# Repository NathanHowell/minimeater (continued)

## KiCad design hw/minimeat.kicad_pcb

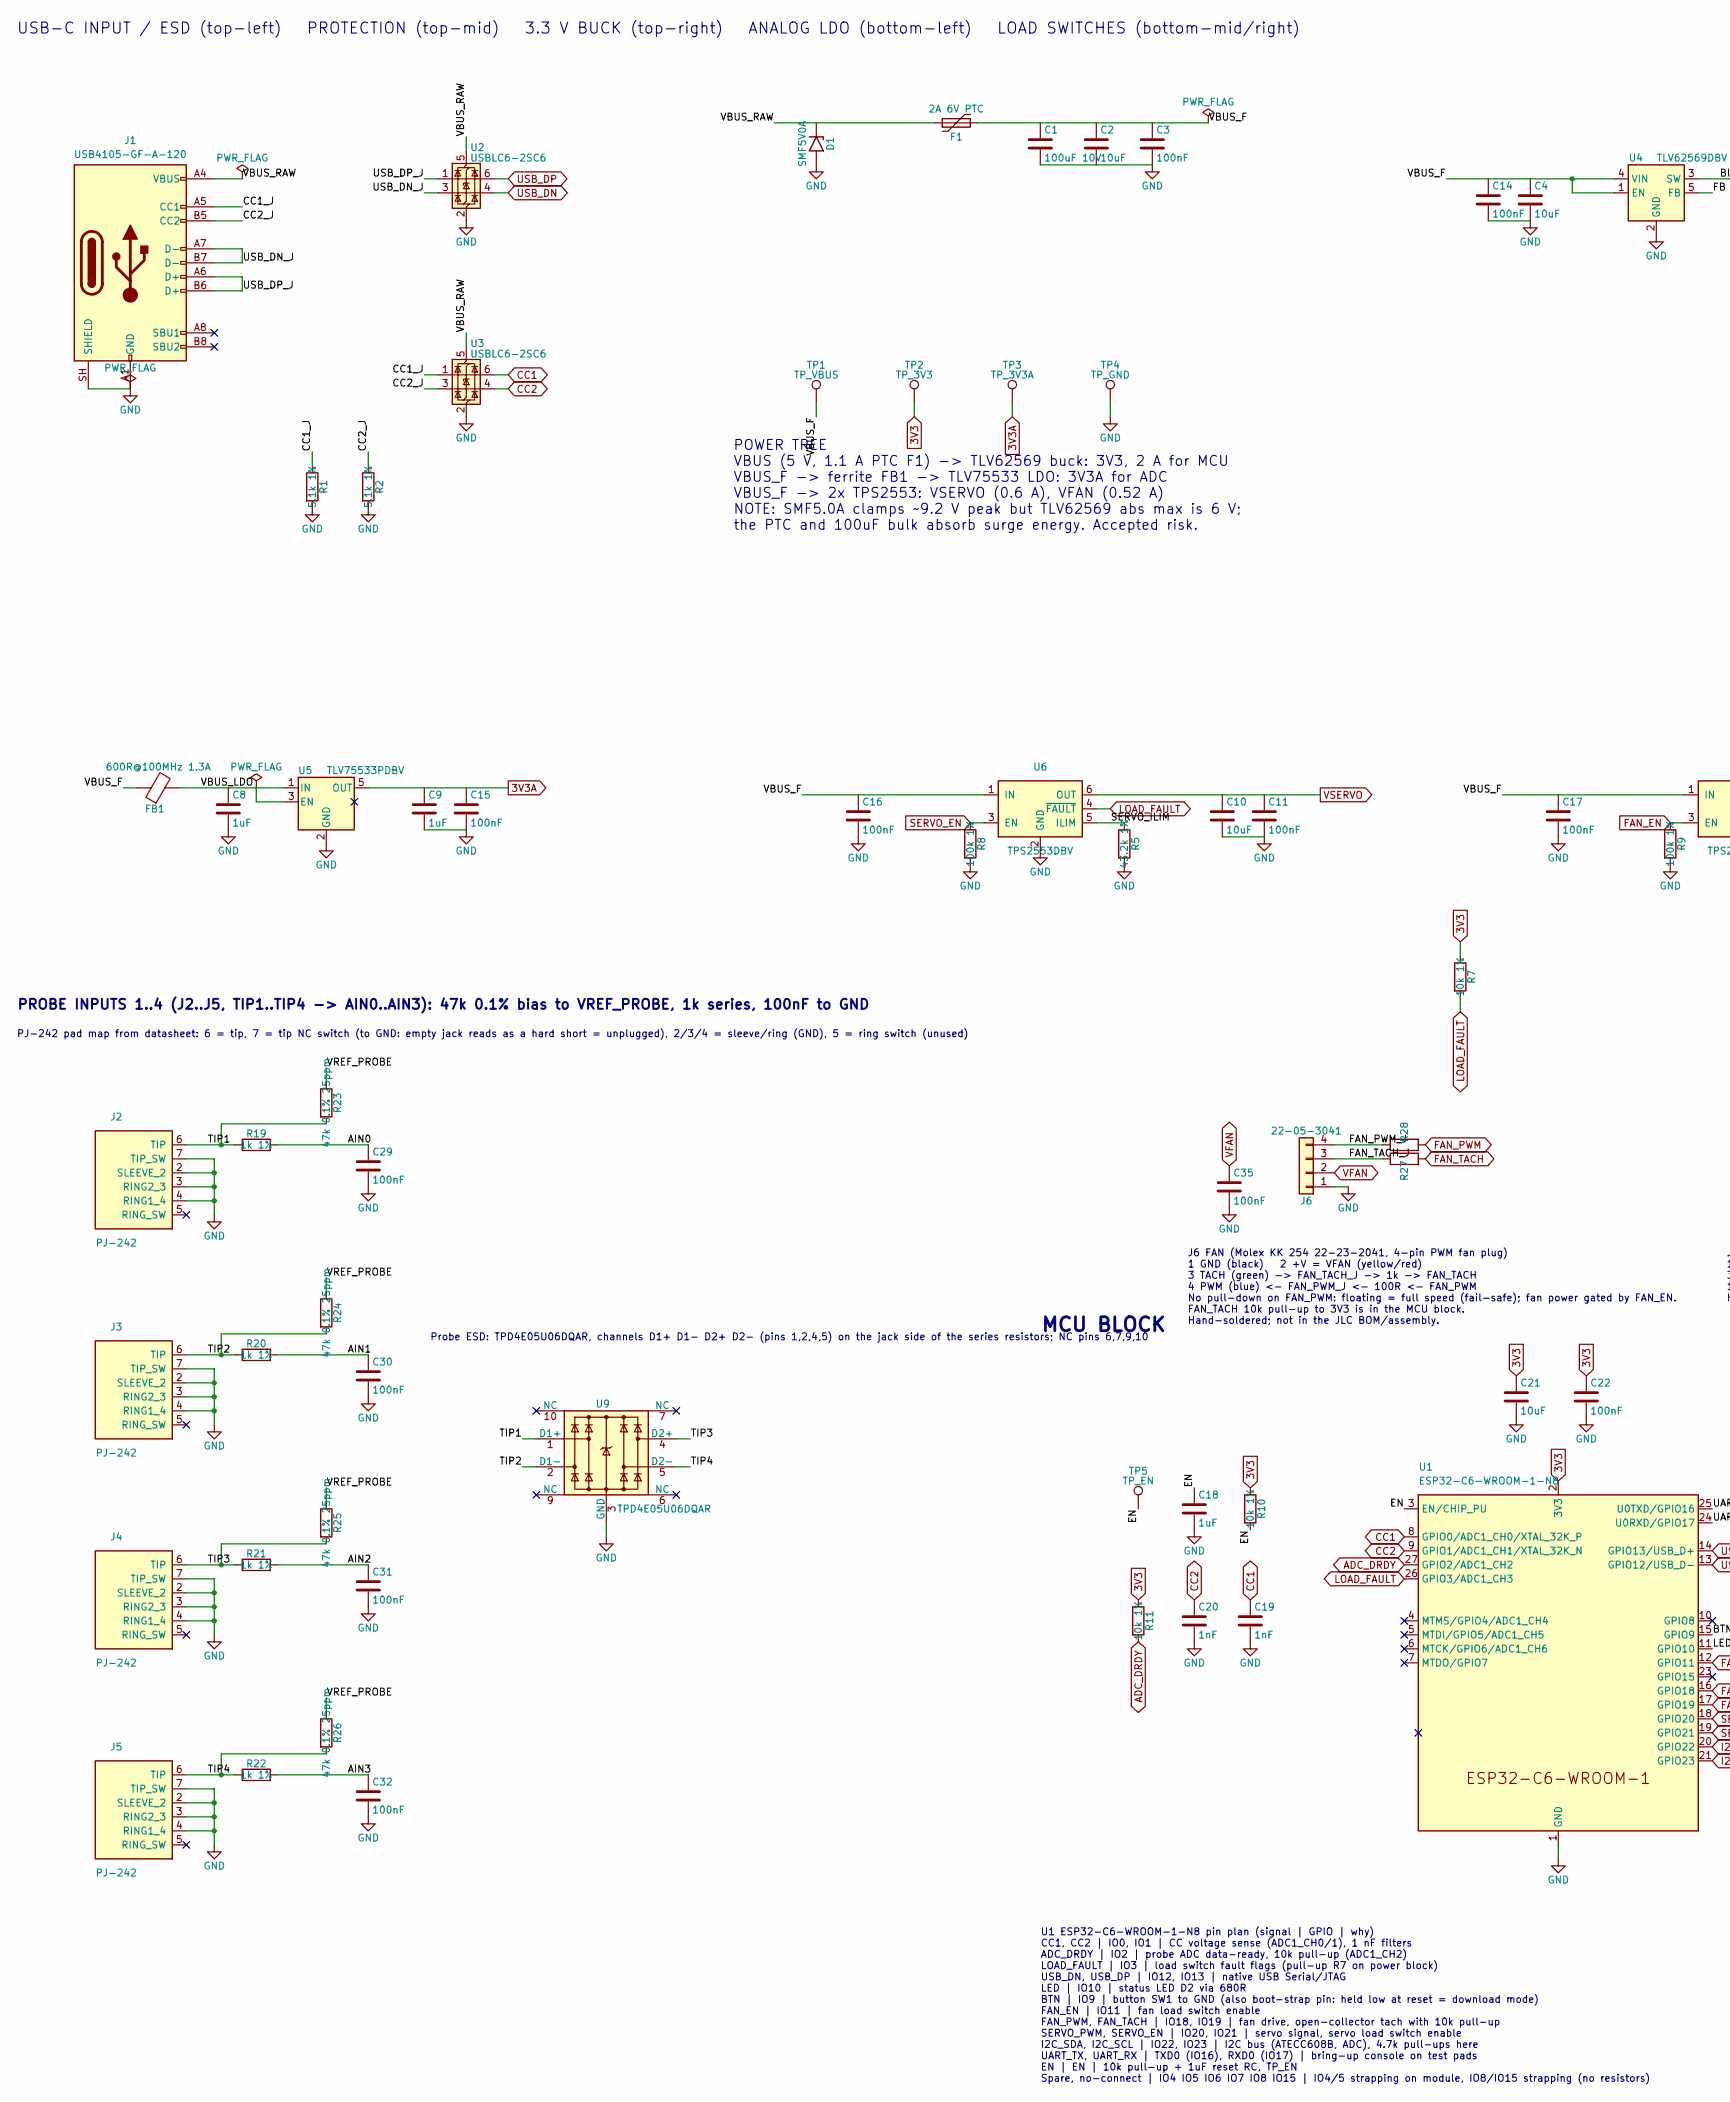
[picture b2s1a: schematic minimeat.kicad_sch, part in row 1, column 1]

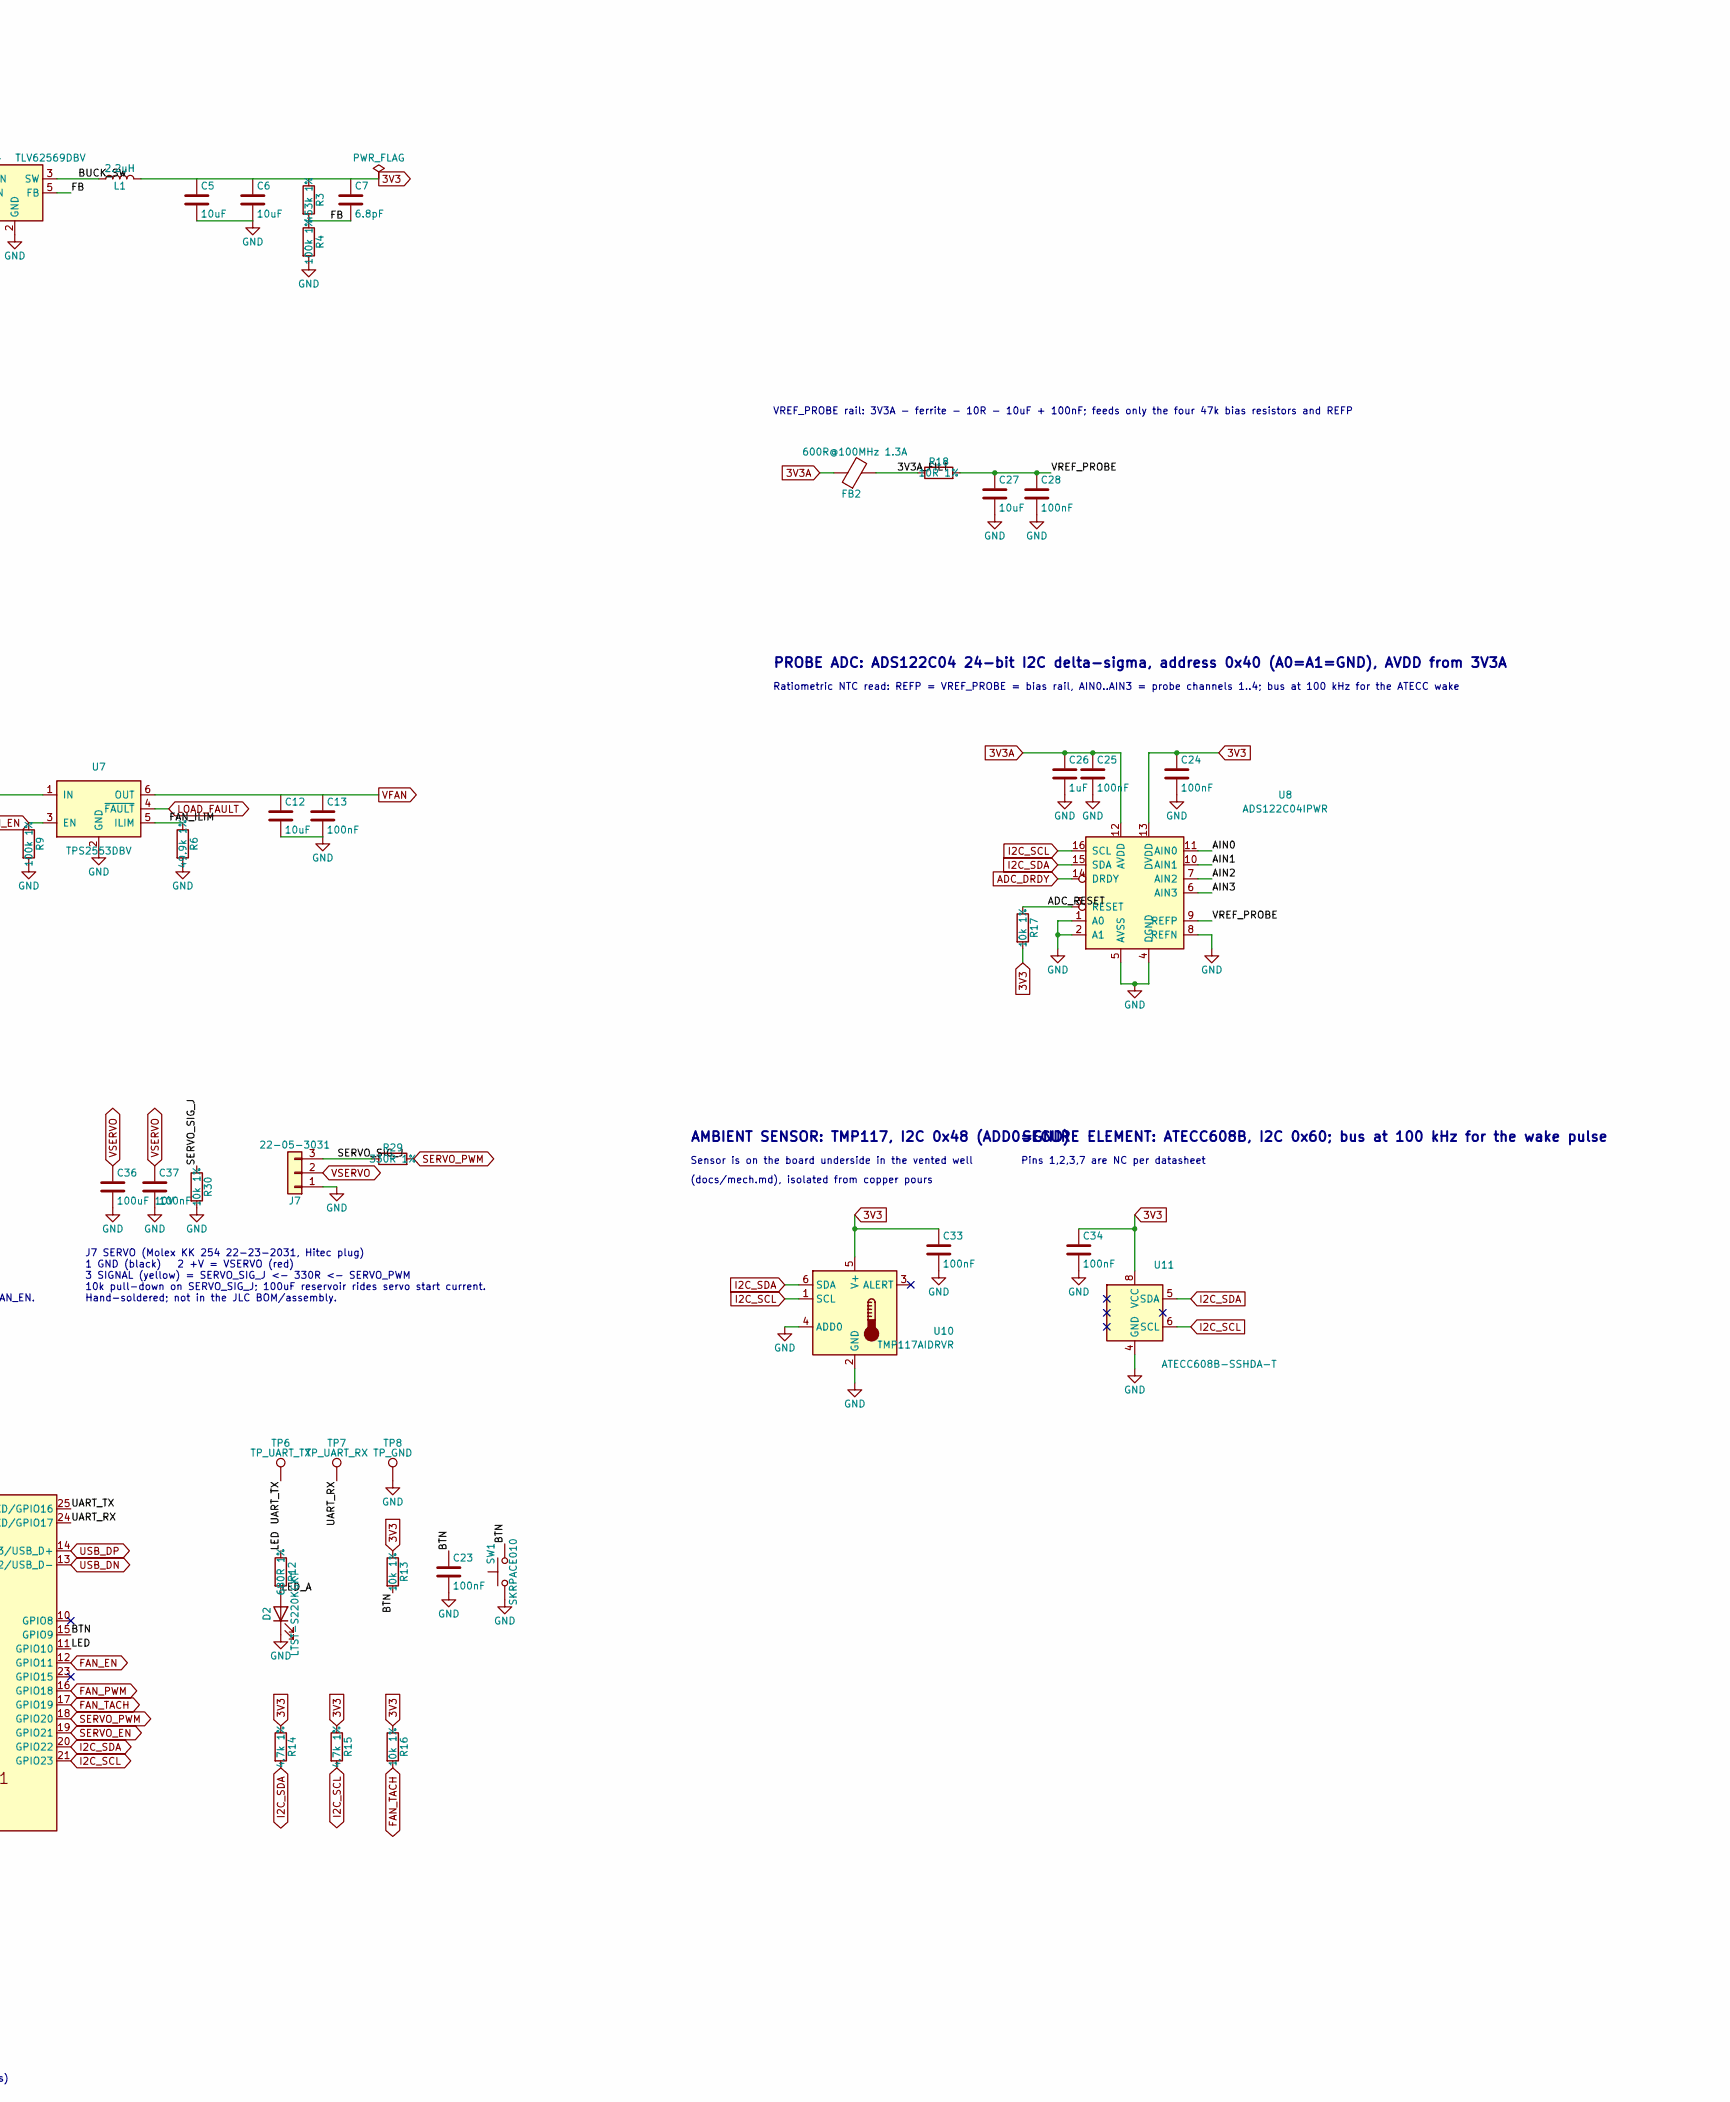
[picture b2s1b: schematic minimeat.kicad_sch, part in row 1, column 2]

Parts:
C1, C36: 100uF 10V; C_1210_3225Metric; LCSC C23742
C2, C4, C5, C6, C10, C12, C21, C27: 10uF; C_0805_2012Metric; LCSC C15850
C3, C11, C13, C14, C15, C16, C17, C22, C23, C24, C25, C28, C29, C30, C31, C32, C33, C34, C35, C37: 100nF; C_0402_1005Metric; LCSC C1525
C7: 6.8pF; C_0402_1005Metric; LCSC C318598
C8, C9, C18, C26: 1uF; C_0402_1005Metric; LCSC C52923
C19, C20: 1nF; C_0402_1005Metric; LCSC C1523
D1: SMF5V0A; D_SMF; LCSC C151296
D2: LTST-S220KGKT; MPN LTST-S220KGKT; LCSC C160469
F1: 2A 6V PTC; Fuse_1206_3216Metric; LCSC C89656
FB1: 600R@100MHz 1.3A; L_0603_1608Metric; LCSC C85833
FB2: 600R@100MHz 1.3A; L_0603_1608Metric; MPN BLM18KG601SN1D; LCSC C85833
J1: USB4105-GF-A-120; USB_C_Receptacle_GCT_USB4105-xx-A_16P_TopMnt_Horizontal; LCSC C5184243
J2, J3, J4, J5: PJ-242; MPN PJ-242; LCSC C431536
J6: 22-05-3041; KK254-RA-04; LCSC N/A hand-solder (Mouser/Digi-Key 22-05-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
J7: 22-05-3031; KK254-RA-03; LCSC N/A hand-solder (Mouser/Digi-Key 22-05-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
L1: 2.2uH; LQH3NPN2R2MMEL; MPN LQH3NPN2R2MMEL; LCSC C668451
R1, R2: 5.1k 1%; R_0402_1005Metric; LCSC C105872
R3: 453k 1%; R_0402_1005Metric; LCSC C27009
R4, R8, R9: 100k 1%; R_0402_1005Metric; LCSC C60491
R5: 43.2k 1%; R_0402_1005Metric; LCSC C137980
R6: 49.9k 1%; R_0402_1005Metric; LCSC C137969
R7, R10, R11, R13, R16, R17, R30: 10k 1%; R_0402_1005Metric; LCSC C60490
R12: 680R 1%; R_0402_1005Metric; MPN RC0402FR-07680RL; LCSC C137948
R14, R15: 4.7k 1%; R_0402_1005Metric; LCSC C25900
R18: 10R 1%; R_0402_1005Metric; LCSC C25077
R19, R20, R21, R22, R27: 1k 1%; R_0402_1005Metric; LCSC C11702
R23, R24, R25, R26: 47k 0.1% 25ppm; R_0603_1608Metric; MPN TNPW060347K0BEEA; LCSC C2089026
R28: 100R 1%; R_0402_1005Metric; LCSC C25076
R29: 330R 1%; R_0402_1005Metric; LCSC C25104
SW1: SKRPACE010; MPN SKRPACE010; LCSC C139797
TP1: TP_VBUS; TestPoint_Pad_D1.5mm; LCSC N/A (not assembled)
TP2: TP_3V3; TestPoint_Pad_D1.5mm; LCSC N/A (not assembled)
TP3: TP_3V3A; TestPoint_Pad_D1.5mm; LCSC N/A (not assembled)
TP4, TP8: TP_GND; TestPoint_Pad_D1.5mm; LCSC N/A (not assembled)
TP5: TP_EN; TestPoint_Pad_D1.5mm; LCSC N/A (not assembled)
TP6: TP_UART_TX; TestPoint_Pad_D1.5mm; LCSC N/A (not assembled)
TP7: TP_UART_RX; TestPoint_Pad_D1.5mm; LCSC N/A (not assembled)
U1: ESP32-C6-WROOM-1-N8; ESP32-C6-WROOM-1; MPN ESP32-C6-WROOM-1-N8; LCSC C5366877
U2, U3: USBLC6-2SC6; SOT-23-6; LCSC C7519
U4: TLV62569DBV; SOT-23-5; LCSC C141836
U5: TLV75533PDBV; SOT-23-5; LCSC C404027
U6, U7: TPS2553DBV; SOT-23-6; LCSC C55266
U8: ADS122C04IPWR; TSSOP-16_4.4x5mm_P0.65mm; MPN ADS122C04IPWR; LCSC C2872338
U9: TPD4E05U06DQAR; TPD4E05U06DQA; MPN TPD4E05U06DQAR; LCSC C138714
U10: TMP117AIDRVR; TMP117AIDRV_WSON-6_noEP; MPN TMP117AIDRVR; LCSC C699536
U11: ATECC608B-SSHDA-T; SOIC-8_3.9x4.9mm_P1.27mm; MPN ATECC608B-SSHDA-T; LCSC C1518769

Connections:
3V3A: C9.1, C15.1, C25.1, C26.1, FB2.1, TP3.1 (1_1), U5.5 (OUT), U8.12 (AVDD)
/3V3A_FILT: FB2.2, R18.1
/ADC_RESET: R17.1, U8.3 (RESET)
/AIN0: C29.1, R19.2, U8.11 (AIN0)
/AIN1: C30.1, R20.2, U8.10 (AIN1)
/AIN2: C31.1, R21.2, U8.7 (AIN2)
/AIN3: C32.1, R22.2, U8.6 (AIN3)
/BTN: C23.1, R13.2, SW1.2, U1.15 (GPIO9)
/BUCK_SW: L1.1, U4.3 (SW)
/CC1_J: J1.A5 (CC1), R1.1, U3.1 (I/O1)
/CC2_J: J1.B5 (CC2), R2.1, U3.3 (I/O2)
/EN: C18.1, R10.2, TP5.1 (1_1), U1.3 (EN/CHIP_PU)
/FAN_ILIM: R6.1, U7.5 (ILIM)
/FAN_PWM_J: J6.4, R28.1
/FAN_TACH_J: J6.3, R27.1
/FB: C7.2, R3.2, R4.1, U4.5 (FB)
/LED: R12.1, U1.11 (GPIO10)
/LED_A: D2.2 (A), R12.2
/SERVO_ILIM: R5.1, U6.5 (ILIM)
/SERVO_SIG_J: J7.3, R29.1, R30.1
/TIP1: J2.6 (TIP), R19.1, R23.2, U9.1 (D1+)
/TIP2: J3.6 (TIP), R20.1, R24.2, U9.2 (D1-)
/TIP3: J4.6 (TIP), R21.1, R25.2, U9.4 (D2+)
/TIP4: J5.6 (TIP), R22.1, R26.2, U9.5 (D2-)
/UART_RX: TP7.1 (1_1), U1.24 (U0RXD/GPIO17)
/UART_TX: TP6.1 (1_1), U1.25 (U0TXD/GPIO16)
/USB_DN_J: J1.A7 (D-), J1.B7 (D-), U2.3 (I/O2)
/USB_DP_J: J1.A6 (D+), J1.B6 (D+), U2.1 (I/O1)
/VREF_PROBE: C27.1, C28.1, R18.2, R23.1, R24.1, R25.1, R26.1, U8.9 (REFP)
ADC_DRDY: R11.2, U1.27 (GPIO2/ADC1_CH2), U8.14 (DRDY)
CC1: C19.1, U1.8 (GPIO0/ADC1_CH0/XTAL_32K_P), U3.6 (I/O1)
CC2: C20.1, U1.9 (GPIO1/ADC1_CH1/XTAL_32K_N), U3.4 (I/O2)
FAN_EN: R9.1, U1.12 (GPIO11), U7.3 (EN)
FAN_PWM: R28.2, U1.16 (GPIO18)
FAN_TACH: R16.2, R27.2, U1.17 (GPIO19)
I2C_SCL: R15.2, U1.21 (GPIO23), U8.16 (SCL), U10.1 (SCL), U11.6 (SCL)
I2C_SDA: R14.2, U1.20 (GPIO22), U8.15 (SDA), U10.6 (SDA), U11.5 (SDA)
LOAD_FAULT: R7.2, U1.26 (GPIO3/ADC1_CH3), U6.4 (~FAULT), U7.4 (~FAULT)
SERVO_EN: R8.1, U1.19 (GPIO21), U6.3 (EN)
SERVO_PWM: R29.2, U1.18 (GPIO20)
USB_DN: U1.13 (GPIO12/USB_D-), U2.4 (I/O2)
USB_DP: U1.14 (GPIO13/USB_D+), U2.6 (I/O1)
VFAN: C12.1, C13.1, C35.1, J6.2, U7.6 (OUT)
VSERVO: C10.1, C11.1, C36.1, C37.1, J7.2, U6.6 (OUT)

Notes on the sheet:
MCU BLOCK
Ratiometric NTC read: REFP = VREF_PROBE = bias rail, AIN0..AIN3 = probe channels 1..4; bus at 100 kHz for the ATECC wake
AMBIENT SENSOR: TMP117, I2C 0x48 (ADD0=GND)
Sensor is on the board underside in the vented well
PROBE INPUTS 1..4 (J2..J5, TIP1..TIP4 -> AIN0..AIN3): 47k 0.1% bias to VREF_PROBE, 1k series, 100nF to GND
Pins 1,2,3,7 are NC per datasheet
Probe ESD: TPD4E05U06DQAR, channels D1+ D1- D2+ D2- (pins 1,2,4,5) on the jack side of the series resistors; NC pins 6,7,9,10
J6 FAN (Molex KK 254 22-23-2041, 4-pin PWM fan plug) 1 GND (black) 2 +V = VFAN (yellow/red) 3 TACH (green) -> FAN_TACH_J -> 1k -> FAN_TACH 4 PWM (blue) <- FAN_PWM_J <- 100R <- FAN_PWM No pull-down on FAN_PWM: floating = full speed (fail-safe); fan power gated by FAN_EN. FAN_TACH 10k pull-up to 3V3 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
USB-C INPUT / ESD (top-left) PROTECTION (top-mid) 3.3 V BUCK (top-right) ANALOG LDO (bottom-left) LOAD SWITCHES (bottom-mid/right)
(docs/mech.md), isolated from copper pours
PROBE ADC: ADS122C04 24-bit I2C delta-sigma, address 0x40 (A0=A1=GND), AVDD from 3V3A
PJ-242 pad map from datasheet: 6 = tip, 7 = tip NC switch (to GND: empty jack reads as a hard short = unplugged), 2/3/4 = sleeve/ring (GND), 5 = ring switch (unused)
U1 ESP32-C6-WROOM-1-N8 pin plan (signal | GPIO | why) CC1, CC2 | IO0, IO1 | CC voltage sense (ADC1_CH0/1), 1 nF filters ADC_DRDY | IO2 | probe ADC data-ready, 10k pull-up (ADC1_CH2) LOAD_FAULT | IO3 | load switch fault flags (pull-up R7 on power block) USB_DN, USB_DP | IO12, IO13 | native USB Seria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
SECURE ELEMENT: ATECC608B, I2C 0x60; bus at 100 kHz for the wake pulse
J7 SERVO (Molex KK 254 22-23-2031, Hitec plug) 1 GND (black) 2 +V = VSERVO (red) 3 SIGNAL (yellow) = SERVO_SIG_J <- 330R <- SERVO_PWM 10k pull-down on SERVO_SIG_J; 100uF reservoir rides servo start current. Hand-soldered; not in the JLC BOM/assembly.
POWER TREE VBUS (5 V, 1.1 A PTC F1) -> TLV62569 buck: 3V3, 2 A for MCU VBUS_F -> ferrite FB1 -> TLV75533 LDO: 3V3A for ADC VBUS_F -> 2x TPS2553: VSERVO (0.6 A), VFAN (0.52 A) NOTE: SMF5.0A clamps ~9.2 V peak but TLV62569 abs max is 6 V; the PTC and 100uF bulk absorb surge energy. Accepted risk.
VREF_PROBE rail: 3V3A - ferrite - 10R - 10uF + 100nF; feeds only the four 47k bias resistors and REFP

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
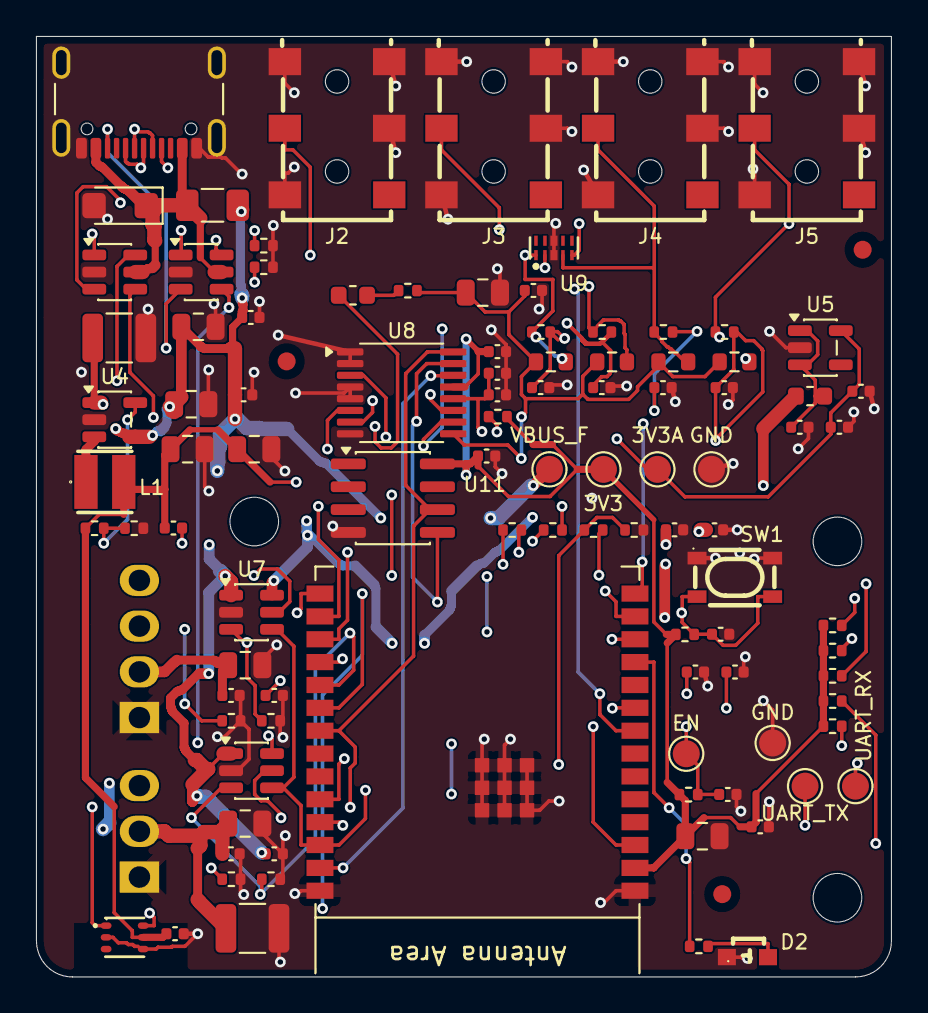
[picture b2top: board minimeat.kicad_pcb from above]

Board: 4 copper layers, 47.5 x 52.2 mm, 106 parts (0 on the bottom side), 49 nets.

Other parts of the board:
FID1, FID2, FID3: Fiducial_1mm_Mask2mm
H1, H2, H3: MountingHole_2.7mm

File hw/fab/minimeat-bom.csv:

Comment,Designator,Footprint,LCSC Part #
100uF 10V,C1 C36,C_1210_3225Metric,C23742
10uF,C2 C4 C5 C6 C10 C12 C21 C27,C_0805_2012Metric,C15850
100nF,C3 C11 C13 C14 C15 C16 C17 C22 C23 C24 C25 C28 C29 C30 C31 C32 C33 C34 C35 C37,C_0402_1005Metric,C1525
6.8pF,C7,C_0402_1005Metric,C318598
1uF,C8 C9 C18 C26,C_0402_1005Metric,C52923
1nF,C19 C20,C_0402_1005Metric,C1523
SMF5V0A,D1,D_SMF,C151296
LTST-S220KGKT,D2,LTST-S220KGKT,C160469
2A 6V PTC,F1,Fuse_1206_3216Metric,C89656
600R@100MHz 1.3A,FB1 FB2,L_0603_1608Metric,C85833
USB4105-GF-A-120,J1,USB_C_Receptacle_GCT_USB4105-xx-A_16P_TopMnt_Horizontal,C5184243
PJ-242,J2 J3 J4 J5,PJ-242,C431536
2.2uH,L1,LQH3NPN2R2MMEL,C668451
5.1k 1%,R1 R2,R_0402_1005Metric,C105872
453k 1%,R3,R_0402_1005Metric,C27009
100k 1%,R4 R8 R9,R_0402_1005Metric,C60491
43.2k 1%,R5,R_0402_1005Metric,C137980
49.9k 1%,R6,R_0402_1005Metric,C137969
10k 1%,R7 R10 R11 R13 R16 R17 R30,R_0402_1005Metric,C60490
680R 1%,R12,R_0402_1005Metric,C137948
4.7k 1%,R14 R15,R_0402_1005Metric,C25900
10R 1%,R18,R_0402_1005Metric,C25077
1k 1%,R19 R20 R21 R22 R27,R_0402_1005Metric,C11702
47k 0.1% 25ppm,R23 R24 R25 R26,R_0603_1608Metric,C2089026
100R 1%,R28,R_0402_1005Metric,C25076
330R 1%,R29,R_0402_1005Metric,C25104
SKRPACE010,SW1,SKRPACE010,C139797
ESP32-C6-WROOM-1-N8,U1,ESP32-C6-WROOM-1,C5366877
USBLC6-2SC6,U2 U3,SOT-23-6,C7519
TLV62569DBV,U4,SOT-23-5,C141836
TLV75533PDBV,U5,SOT-23-5,C404027
TPS2553DBV,U6 U7,SOT-23-6,C55266
ADS122C04IPWR,U8,TSSOP-16_4.4x5mm_P0.65mm,C2872338
TPD4E05U06DQAR,U9,TPD4E05U06DQA,C138714
TMP117AIDRVR,U10,TMP117AIDRV_WSON-6_noEP,C699536
ATECC608B-SSHDA-T,U11,SOIC-8_3.9x4.9mm_P1.27mm,C1518769

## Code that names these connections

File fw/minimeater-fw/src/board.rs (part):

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//! the only place that knows pin numbers and peripheral instances.
//!
//! Pin map: the schematic's contract (`.3.3`; hw/minimeater.kicad_sch). Constraints honoured (ADR 0001): CC sense
//! on ADC1 pins (GPIO0-6), button on GPIO9 (BOOT), nothing on GPIO8 (strapping) or GPIO12/13 (USB). The probe jacks' rings are
//! GPIO7, 6, 5 and 4 for jacks 1-4 (smart probes, minimeat-098): not driven yet.
//!
//! | Signal | GPIO | | Signal | GPIO |
//! |---|---|---|---|---|
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use esp_hal::ledc::timer::{self, TimerIFace};
use esp_hal::ledc::{LSGlobalClkSource, Ledc, LowSpeed};
use esp_hal::pcnt::{Pcnt, channel::EdgeMode, unit::Unit};
use esp_hal::peripherals::{ADC1, FROM_CPU_INTR0, GPIO0, GPIO1, GPIO2, Peripherals, TIMG0, TIMG1, USB_DEVICE, WIFI};
use esp_hal::time::{Duration, Rate};
use esp_hal::timer::timg::{MwdtStage, TimerGroup, Wdt};
use esp_storage::FlashStorage;
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        esp_hal::i2c::master::Config::default().with_frequency(Rate::from_khz(100)),
    )
    .expect("i2c config")
    .with_sda(p.GPIO23)
    .with_scl(p.GPIO22)
    .into_async();
    static I2C_BUS: StaticCell<Mutex<CriticalSectionRawMutex, I2c<'static, Async>>> = StaticCell::new();
    let i2c = I2C_BUS.init(Mutex::new(i2c));
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            frequency: Rate::from_hz(1_000_000 / SERVO_PERIOD_US),
        })
        .expect("servo timer");
    let mut fan = ledc.channel(channel::Number::Channel0, p.GPIO18);
    fan.configure(channel::config::Config {
        timer: fan_timer,
        duty_pct: 0,
        drive_mode: DriveMode::PushPull,
    })
    .expect("fan channel");
    let mut servo = ledc.channel(channel::Number::Channel1, p.GPIO20);
    servo
        .configure(channel::config::Config {
            timer: servo_timer,
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
    static PCNT: StaticCell<Pcnt<'static>> = StaticCell::new();
    let pcnt = PCNT.init(Pcnt::new(p.PCNT));
    let tach_pin = Input::new(p.GPIO19, InputConfig::default().with_pull(Pull::Up));
    let unit = &pcnt.unit0;
    unit.set_filter(Some(1023)).expect("tach filter");
    unit.channel0.set_edge_signal(tach_pin.peripheral_input());
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
    // ADC1 reads the CC pins and the servo current: one converter, shared by the two readers (both in the actuator task)
    let mut adc_cfg = AdcConfig::new();
    let cc1 = adc_cfg.enable_pin_with_cal::<_, AdcCalCurve<ADC1<'static>>>(p.GPIO0, Attenuation::_11dB);
    let cc2 = adc_cfg.enable_pin_with_cal::<_, AdcCalCurve<ADC1<'static>>>(p.GPIO1, Attenuation::_11dB);
    // 0 to 1.8 V (0.9 A) from the INA181; 11 dB reads to about 3.1 V
    let isense = adc_cfg.enable_pin_with_cal::<_, AdcCalCurve<ADC1<'static>>>(p.GPIO2, Attenuation::_11dB);
    static ADC: StaticCell<SharedAdc> = StaticCell::new();
    let adc = &*ADC.init(BlockingMutex::new(RefCell::new(Adc::new(p.ADC1, adc_cfg))));

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        fan,
        tach: PcntTach { unit, since: None },
        servo: PwmServo::new(servo, SERVO_PERIOD_US),
        servo_power: Output::new(p.GPIO21, Level::Low, out),
        fan_power: Output::new(p.GPIO11, Level::Low, out),
        // the shared open-drain fault line has its own pull-up on the board
        load_fault: Input::new(p.GPIO3, InputConfig::default().with_pull(Pull::None)),
        servo_current: ServoSense { adc, pin: isense },
        led: Output::new(p.GPIO10, Level::Low, out),
        button: Input::new(p.GPIO9, InputConfig::default().with_pull(Pull::Up)),
        config: FlashRegion::new::<CONFIG_OFFSET, CONFIG_LEN>(BlockingAsync::new(FlashStorage::new(p.FLASH))),
        usb: CcSense { adc, cc1, cc2 },
        // TIMG0 is the runtime's; TIMG1's watchdog resets the whole system
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/// CC1/CC2 voltages across the 5.1k Rd pull-downs.
pub struct CcSense {
    adc: &'static SharedAdc,
    cc1: CcPin<GPIO0<'static>>,
    cc2: CcPin<GPIO1<'static>>,
}

impl UsbPower for CcSense {
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/// The servo's supply current: the INA181's output across the shunt (2 mV per mA).
pub struct ServoSense {
    adc: &'static SharedAdc,
    pin: CcPin<GPIO2<'static>>,
}

impl ServoCurrent for ServoSense {
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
